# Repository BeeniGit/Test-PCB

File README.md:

# Test-PCB

```wave
<WaveDormHeader>
  {signal: [
    {name: 'clk', wave: 'p.....|...'},
    {name: 'dat', wave: 'x.345x|=.x', data: ['head', 'body', 'tail', 'data']},
    {name: 'req', wave: '0.1..0|1.0'},
    {},
    {name: 'ack', wave: '1.....|01.'}
  ]}
</WaveDormHeader>
```

```mermaid
graph LR
  A --> B;
  B --> A;
```

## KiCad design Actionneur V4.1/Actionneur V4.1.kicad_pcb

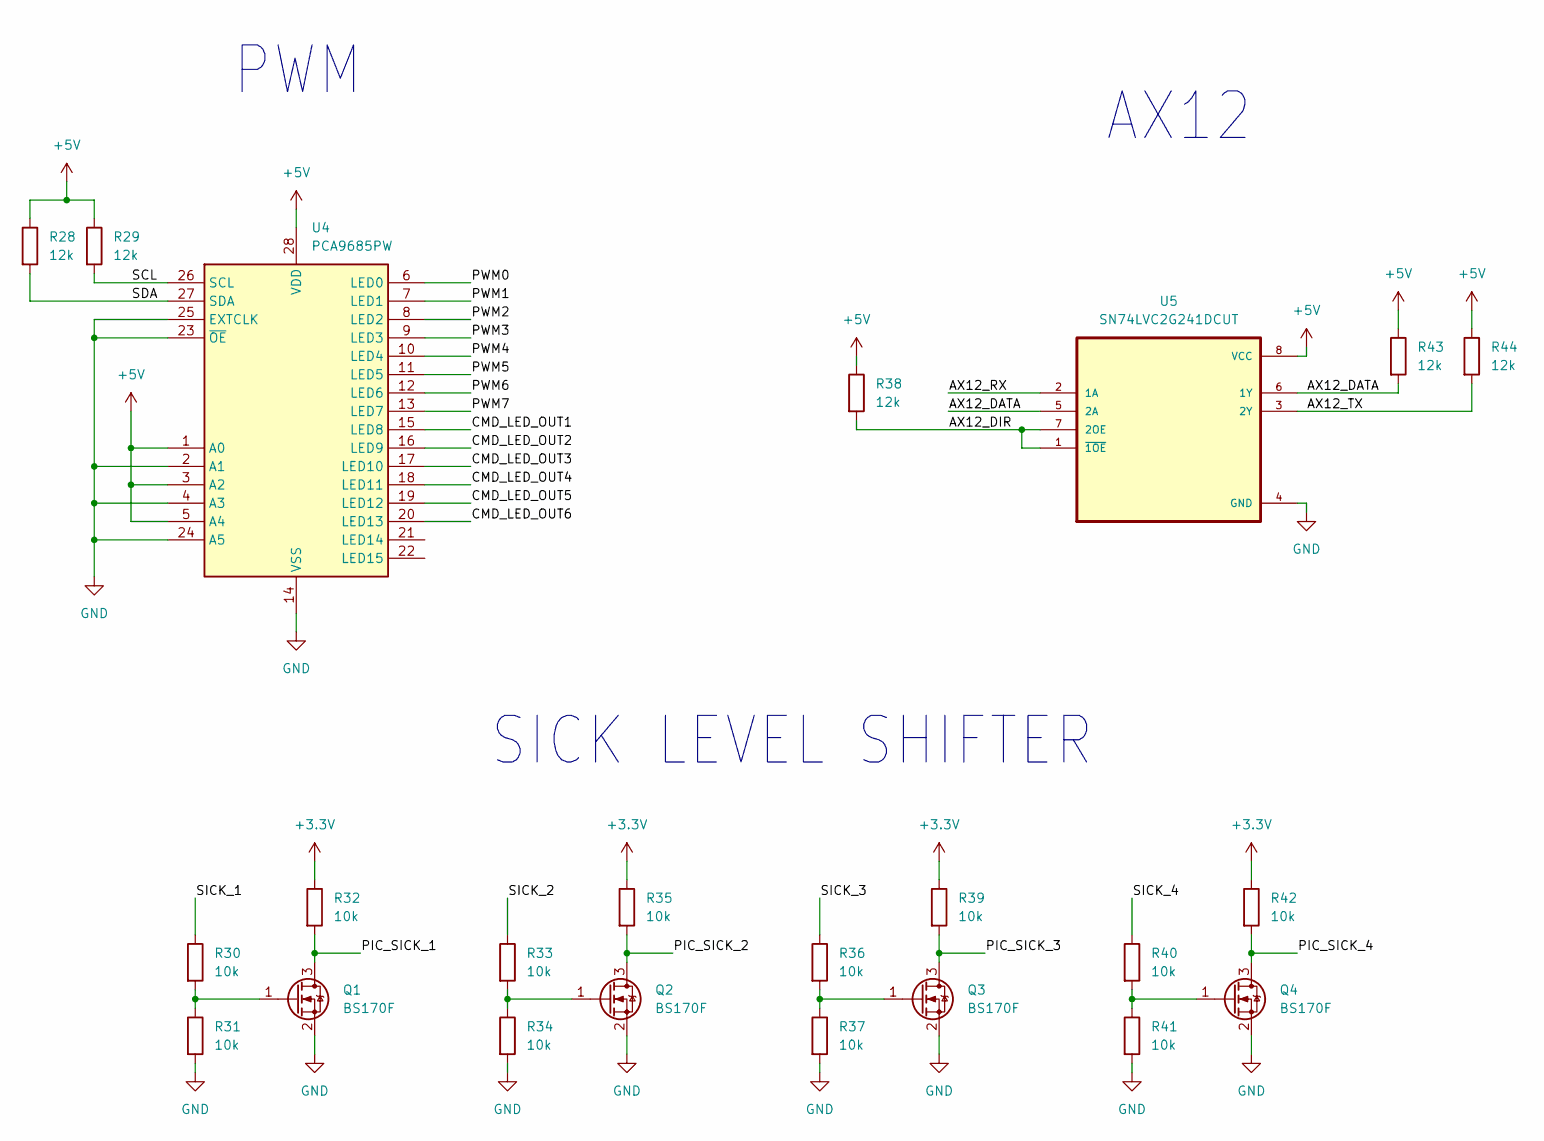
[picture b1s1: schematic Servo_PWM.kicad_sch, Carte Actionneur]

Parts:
Q1, Q2, Q3, Q4: BS170F; SOT-23
R28, R29, R38, R43, R44: 12k; R_0805_2012Metric
R30, R31, R32, R33, R34, R35, R36, R37, R39, R40, R41, R42: 10k; R_0805_2012Metric
U4: PCA9685PW; TSSOP-28_4.4x9.7mm_P0.65mm
U5: SN74LVC2G241DCUT; SOP50P310X90-8N

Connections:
+5V: R28.1, R29.1, R38.1, R43.1, R44.1, U4.1 (A0), U4.3 (A2), U4.5 (A4), U4.28 (VDD), U5.8 (VCC); also elsewhere on the board
/Servo_PWM/AX12_DATA: R43.2, U5.5 (2A), U5.6 (1Y)
/Servo_PWM/AX12_DIR: R38.2, U5.1 (~1OE), U5.7 (2OE)
/Servo_PWM/AX12_RX: U5.2 (1A)
/Servo_PWM/AX12_TX: R44.2, U5.3 (2Y)
/Servo_PWM/CMD_LED_OUT1: U4.15 (LED8)
/Servo_PWM/CMD_LED_OUT2: U4.16 (LED9)
/Servo_PWM/CMD_LED_OUT3: U4.17 (LED10)
/Servo_PWM/CMD_LED_OUT4: U4.18 (LED11)
/Servo_PWM/CMD_LED_OUT5: U4.19 (LED12)
/Servo_PWM/CMD_LED_OUT6: U4.20 (LED13)
/Servo_PWM/PIC_SICK_1: Q1.3 (D), R32.2
/Servo_PWM/PIC_SICK_2: Q2.3 (D), R35.2
/Servo_PWM/PIC_SICK_3: Q3.3 (D), R39.2
/Servo_PWM/PIC_SICK_4: Q4.3 (D), R42.2
/Servo_PWM/PWM0: U4.6 (LED0)
/Servo_PWM/PWM1: U4.7 (LED1)
/Servo_PWM/PWM2: U4.8 (LED2)
/Servo_PWM/PWM3: U4.9 (LED3)
/Servo_PWM/PWM4: U4.10 (LED4)
/Servo_PWM/PWM5: U4.11 (LED5)
/Servo_PWM/PWM6: U4.12 (LED6)
/Servo_PWM/PWM7: U4.13 (LED7)
/Servo_PWM/SCL: R29.2, U4.26 (SCL)
/Servo_PWM/SDA: R28.2, U4.27 (SDA)
/Servo_PWM/SICK_1: R30.1
/Servo_PWM/SICK_2: R33.1
/Servo_PWM/SICK_3: R36.1
/Servo_PWM/SICK_4: R40.1
GND: Q1.2 (S), Q2.2 (S), Q3.2 (S), Q4.2 (S), R31.2, R34.2, R37.2, R41.2, U4.2 (A1), U4.4 (A3), U4.14 (VSS), U4.23 (~OE), U4.24 (A5), U4.25 (EXTCLK), U5.4 (GND); also elsewhere on the board
unnamed: Q1.1 (G), R30.2, R31.1
unnamed: Q2.1 (G), R33.2, R34.1
unnamed: Q3.1 (G), R36.2, R37.1
unnamed: Q4.1 (G), R40.2, R41.1

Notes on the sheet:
AX12
SICK LEVEL SHIFTER
PWM

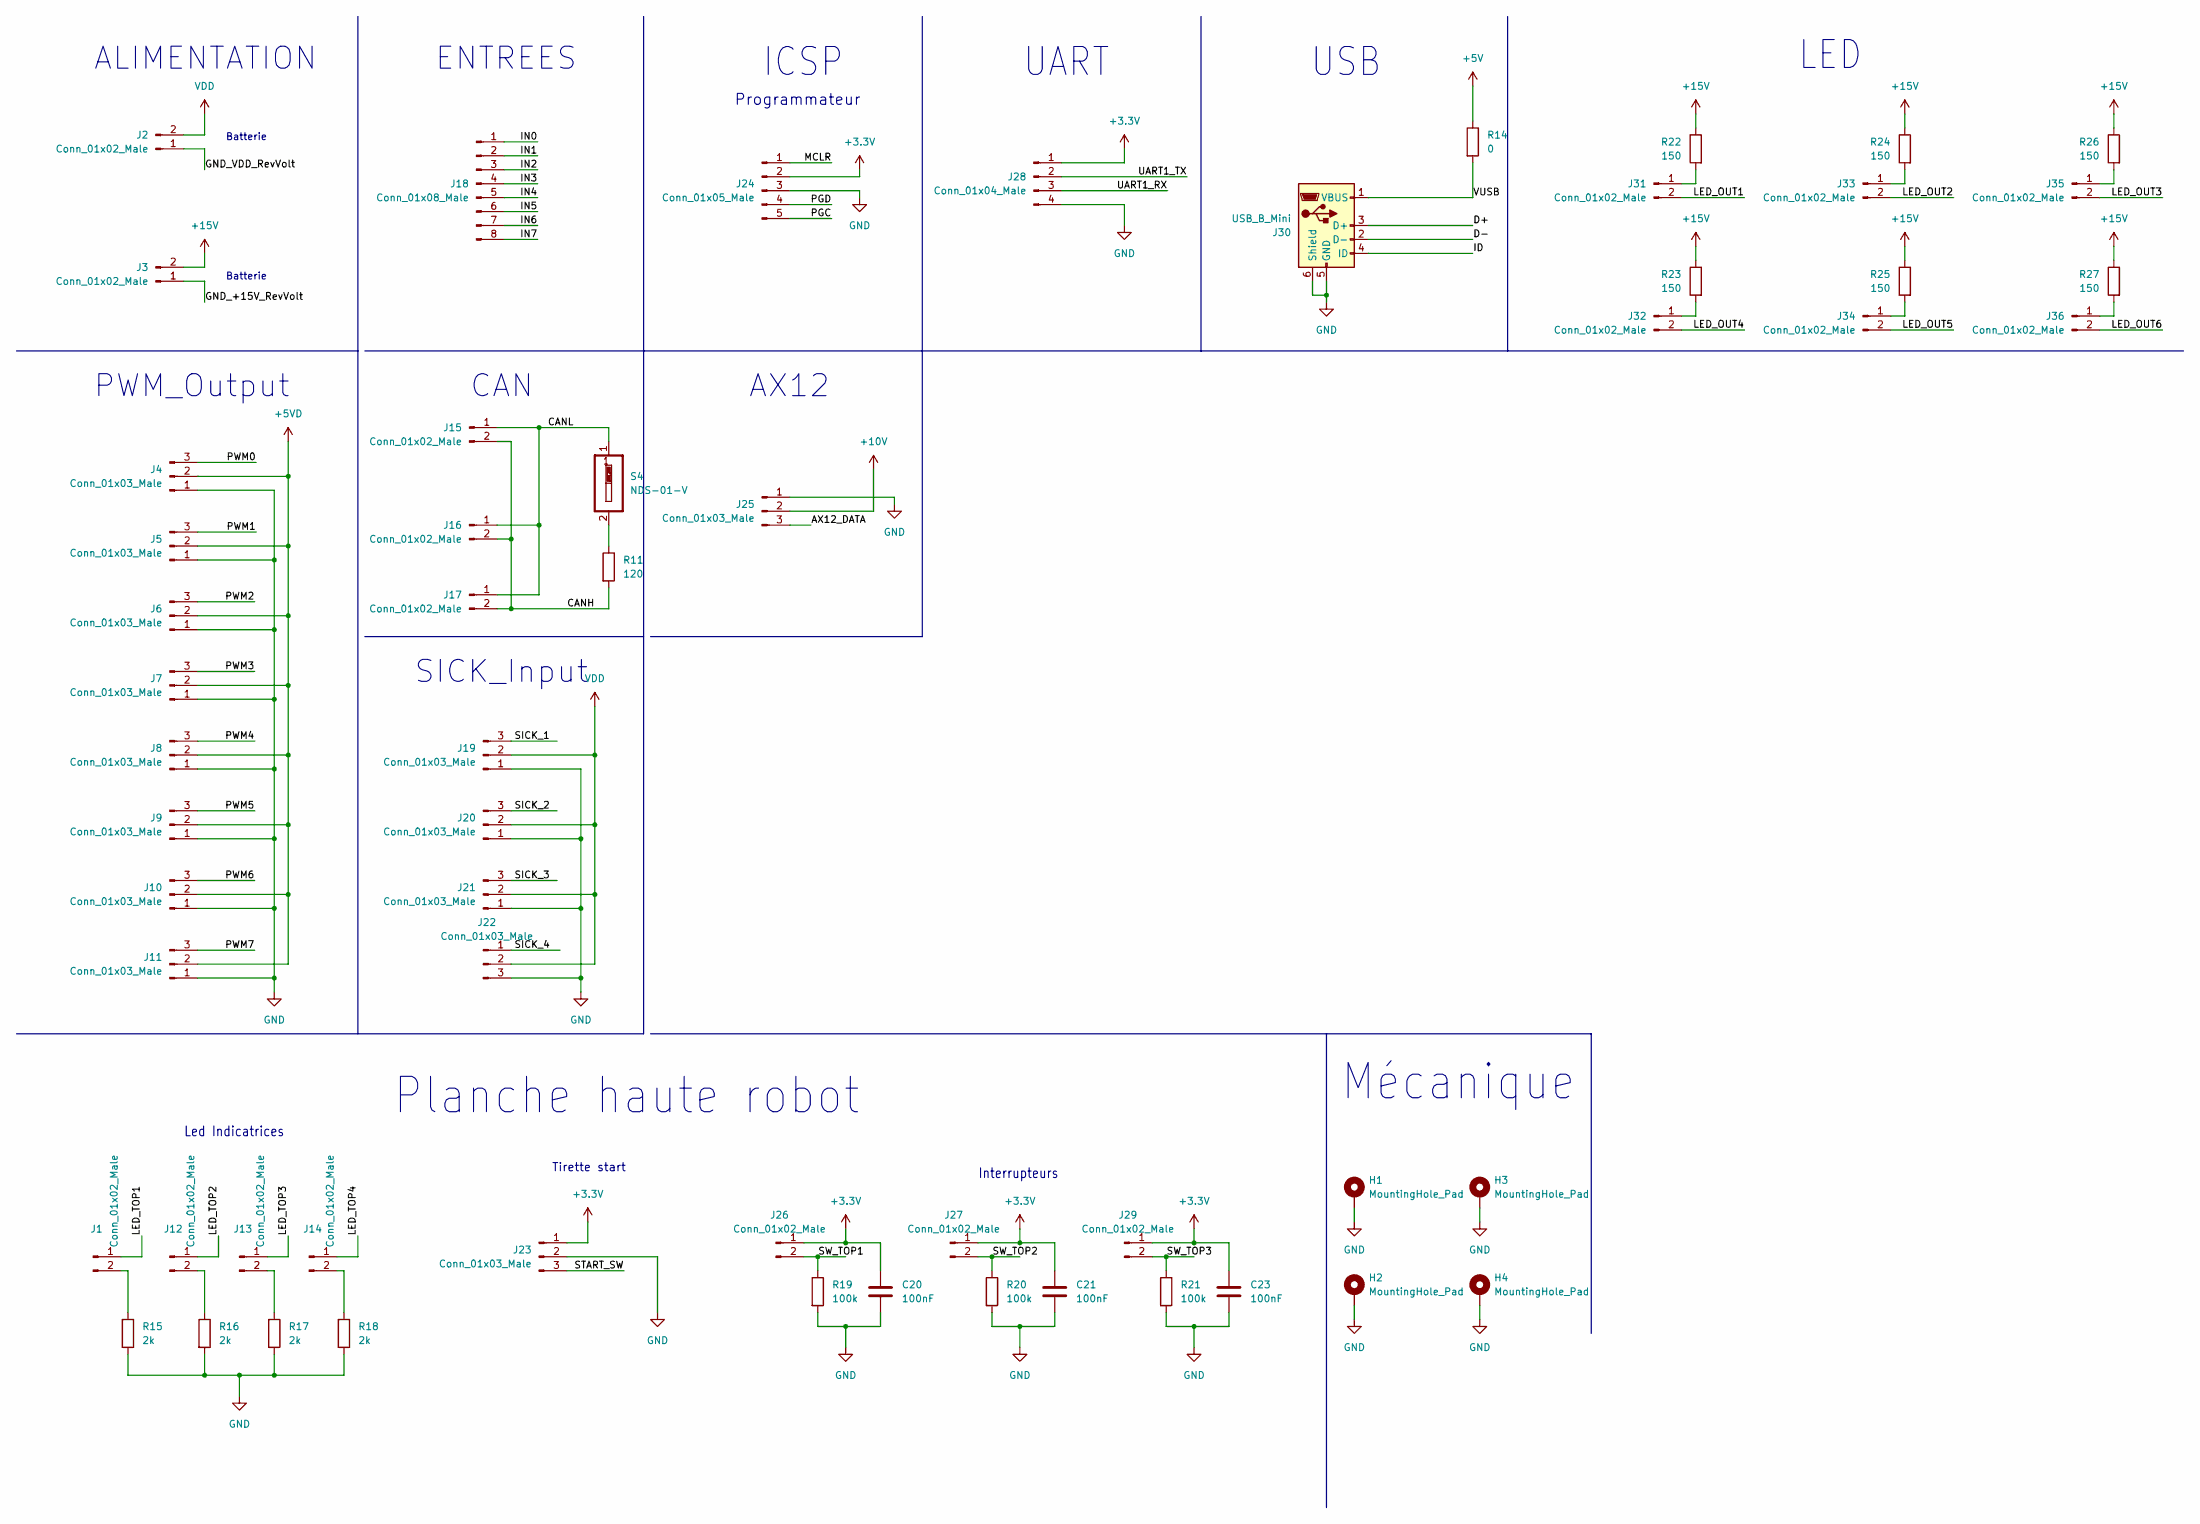
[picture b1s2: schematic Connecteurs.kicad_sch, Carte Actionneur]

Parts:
C20, C21, C23: 100nF; C_0805_2012Metric
H1, H2, H3, H4: MountingHole_Pad; MountingHole_2.2mm_M2_ISO14580_Pad
J1, J12, J13, J14, J15, J16, J17, J26, J27, J29, J31, J32, J33, J34, J35, J36: Conn_01x02_Male; FanPinHeader_1x02_P2.54mm_Vertical
J2, J3: Conn_01x02_Male; PhoenixContact_MSTBA_2,5_2-G_1x02_P5.00mm_Horizontal
J4, J5, J6, J7, J8, J9, J10, J11, J19, J20, J21, J22, J23, J25: Conn_01x03_Male; FanPinHeader_1x03_P2.54mm_Vertical
J18: Conn_01x08_Male; PinHeader_1x08_P2.54mm_Vertical
J24: Conn_01x05_Male; PinSocket_1x05_P2.54mm_Vertical
J28: Conn_01x04_Male; PinHeader_1x04_P2.54mm_Vertical
J30: USB_B_Mini; USB_Mini-B_Wuerth_65100516121_Horizontal
R11: 120; R_0805_2012Metric
R14: 0; R_0805_2012Metric
R15, R16, R17, R18: 2k; R_0805_2012Metric
R19, R20, R21: 100k; R_0805_2012Metric
R22, R23, R24, R25, R26, R27: 150; R_0805_2012Metric
S4: NDS-01-V; DIP762W60P254L390H705Q2N; Manufacturer_Part_Number NDS-01-V

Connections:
+5V: R14.1; also elsewhere on the board
+5VD: J4.2, J5.2, J6.2, J7.2, J8.2, J9.2, J10.2, J11.2; also elsewhere on the board
+10V: J25.2; also elsewhere on the board
+15V: J3.2, R22.1, R23.1, R24.1, R25.1, R26.1, R27.1; also elsewhere on the board
/Connecteurs/AX12_DATA: J25.3
/Connecteurs/CANH: J15.2, J16.2, J17.2, R11.2
/Connecteurs/CANL: J15.1, J16.1, J17.1, S4.1
/Connecteurs/D+: J30.3 (D+)
/Connecteurs/D-: J30.2 (D-)
/Connecteurs/GND_+15V_RevVolt: J3.1
/Connecteurs/GND_VDD_RevVolt: J2.1
/Connecteurs/ID: J30.4 (ID)
/Connecteurs/IN0: J18.1
/Connecteurs/IN1: J18.2
/Connecteurs/IN2: J18.3
/Connecteurs/IN3: J18.4
/Connecteurs/IN4: J18.5
/Connecteurs/IN5: J18.6
/Connecteurs/IN6: J18.7
/Connecteurs/IN7: J18.8
/Connecteurs/LED_OUT1: J31.2
/Connecteurs/LED_OUT2: J33.2
/Connecteurs/LED_OUT3: J35.2
/Connecteurs/LED_OUT4: J32.2
/Connecteurs/LED_OUT5: J34.2
/Connecteurs/LED_OUT6: J36.2
/Connecteurs/LED_TOP1: J1.1
/Connecteurs/LED_TOP2: J12.1
/Connecteurs/LED_TOP3: J13.1
/Connecteurs/LED_TOP4: J14.1
/Connecteurs/MCLR: J24.1
/Connecteurs/PGC: J24.5
/Connecteurs/PGD: J24.4
/Connecteurs/PWM0: J4.3
/Connecteurs/PWM1: J5.3
/Connecteurs/PWM2: J6.3
/Connecteurs/PWM3: J7.3
/Connecteurs/PWM4: J8.3
/Connecteurs/PWM5: J9.3
/Connecteurs/PWM6: J10.3
/Connecteurs/PWM7: J11.3
/Connecteurs/SICK_1: J19.3
/Connecteurs/SICK_2: J20.3
/Connecteurs/SICK_3: J21.3
/Connecteurs/SICK_4: J22.1
/Connecteurs/START_SW: J23.3
/Connecteurs/SW_TOP1: J26.2, R19.1
/Connecteurs/SW_TOP2: J27.2, R20.1
/Connecteurs/SW_TOP3: J29.2, R21.1
/Connecteurs/UART1_RX: J28.3
/Connecteurs/UART1_TX: J28.2
/Connecteurs/VUSB: J30.1 (VBUS), R14.2
GND: C20.2, C21.2, C23.2, H1.1, H2.1, H3.1, H4.1, J4.1, J5.1, J6.1, J7.1, J8.1, J9.1, J10.1, J11.1, J19.1, J20.1, J21.1, J22.3, J23.2, J24.3, J25.1, J28.4, J30.5 (GND), J30.6 (Shield), R15.2, R16.2, R17.2, R18.2, R19.2, R20.2, R21.2; also elsewhere on the board
unnamed: J1.2, R15.1
unnamed: J12.2, R16.1
unnamed: J13.2, R17.1
unnamed: J14.2, R18.1
unnamed: J31.1, R22.2
unnamed: J32.1, R23.2
unnamed: J33.1, R24.2
unnamed: J34.1, R25.2
unnamed: J35.1, R26.2
unnamed: J36.1, R27.2
unnamed: R11.1, S4.2
VDD: J2.2, J19.2, J20.2, J21.2, J22.2; also elsewhere on the board

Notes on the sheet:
UART
ENTREES
Batterie
CAN
ICSP
SICK_Input
PWM_Output
Led Indicatrices
LED
Interrupteurs
Batterie
Planche haute robot
Mécanique
USB
AX12
ALIMENTATION
Programmateur
Tirette start

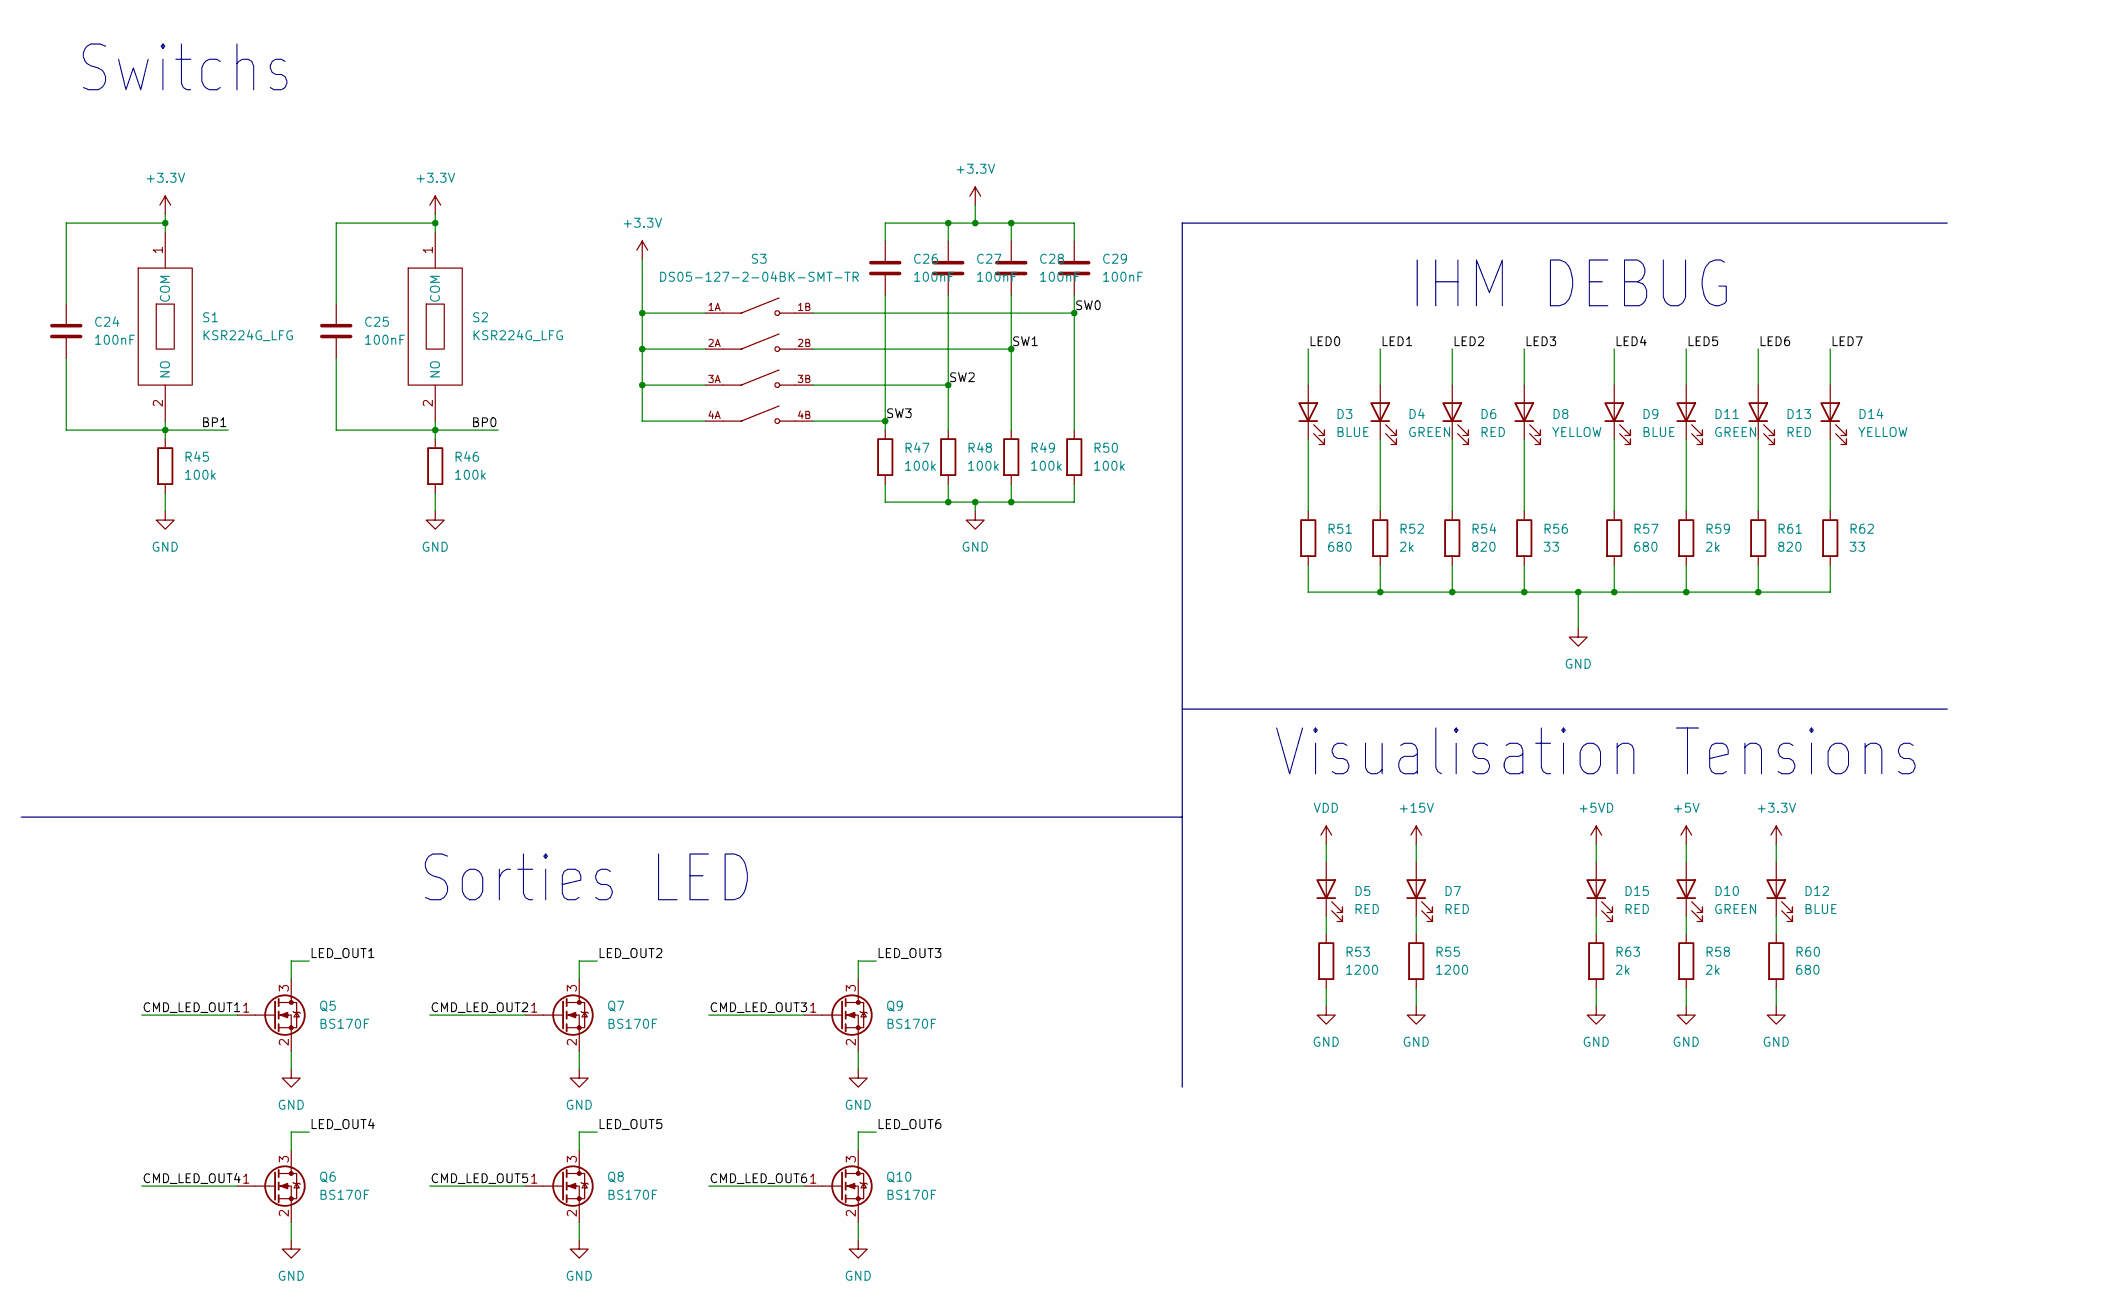
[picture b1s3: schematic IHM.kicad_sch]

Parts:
C24, C25, C26, C27, C28, C29: 100nF; C_0805_2012Metric
D3, D9, D12: BLUE; LED_0805_2012Metric
D4, D10, D11: GREEN; LED_0805_2012Metric
D5, D6, D7, D13, D15: RED; LED_0805_2012Metric
D8, D14: YELLOW; LED_0805_2012Metric
Q5, Q6, Q7, Q8, Q9, Q10: BS170F; SOT-23
R45, R46, R47, R48, R49, R50: 100k; R_0805_2012Metric
R51, R57, R60: 680; R_0805_2012Metric
R52, R58, R59, R63: 2k; R_0805_2012Metric
R53, R55: 1200; R_0805_2012Metric
R54, R61: 820; R_0805_2012Metric
R56, R62: 33; R_0805_2012Metric
S1, S2: KSR224G_LFG; KSR224GLFG; Manufacturer_Part_Number KSR224G LFG
S3: DS05-127-2-04BK-SMT-TR; SW_DS05-127-2-04BK-SMT-TR; PARTREV V0.0

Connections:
+5V: D10.2 (A); also elsewhere on the board
+5VD: D15.2 (A); also elsewhere on the board
+15V: D7.2 (A); also elsewhere on the board
/IHM/BP0: C25.2, R46.1, S2.2 (NO)
/IHM/BP1: C24.2, R45.1, S1.2 (NO)
/IHM/CMD_LED_OUT1: Q5.1 (G)
/IHM/CMD_LED_OUT2: Q7.1 (G)
/IHM/CMD_LED_OUT3: Q9.1 (G)
/IHM/CMD_LED_OUT4: Q6.1 (G)
/IHM/CMD_LED_OUT5: Q8.1 (G)
/IHM/CMD_LED_OUT6: Q10.1 (G)
/IHM/LED0: D3.2 (A)
/IHM/LED1: D4.2 (A)
/IHM/LED2: D6.2 (A)
/IHM/LED3: D8.2 (A)
/IHM/LED4: D9.2 (A)
/IHM/LED5: D11.2 (A)
/IHM/LED6: D13.2 (A)
/IHM/LED7: D14.2 (A)
/IHM/LED_OUT1: Q5.3 (D)
/IHM/LED_OUT2: Q7.3 (D)
/IHM/LED_OUT3: Q9.3 (D)
/IHM/LED_OUT4: Q6.3 (D)
/IHM/LED_OUT5: Q8.3 (D)
/IHM/LED_OUT6: Q10.3 (D)
/IHM/SW3: C26.2, R47.1, S3.4B
GND: Q5.2 (S), Q6.2 (S), Q7.2 (S), Q8.2 (S), Q9.2 (S), Q10.2 (S), R45.2, R46.2, R47.2, R48.2, R49.2, R50.2, R51.2, R52.2, R53.2, R54.2, R55.2, R56.2, R57.2, R58.2, R59.2, R60.2, R61.2, R62.2, R63.2; also elsewhere on the board
unnamed: D3.1 (K), R51.1
unnamed: D4.1 (K), R52.1
unnamed: D5.1 (K), R53.1
unnamed: D6.1 (K), R54.1
unnamed: D7.1 (K), R55.1
unnamed: D8.1 (K), R56.1
unnamed: D9.1 (K), R57.1
unnamed: D10.1 (K), R58.1
unnamed: D11.1 (K), R59.1
unnamed: D12.1 (K), R60.1
unnamed: D13.1 (K), R61.1
unnamed: D14.1 (K), R62.1
unnamed: D15.1 (K), R63.1
VDD: D5.2 (A); also elsewhere on the board

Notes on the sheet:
Switchs
IHM DEBUG
Sorties LED
Visualisation Tensions

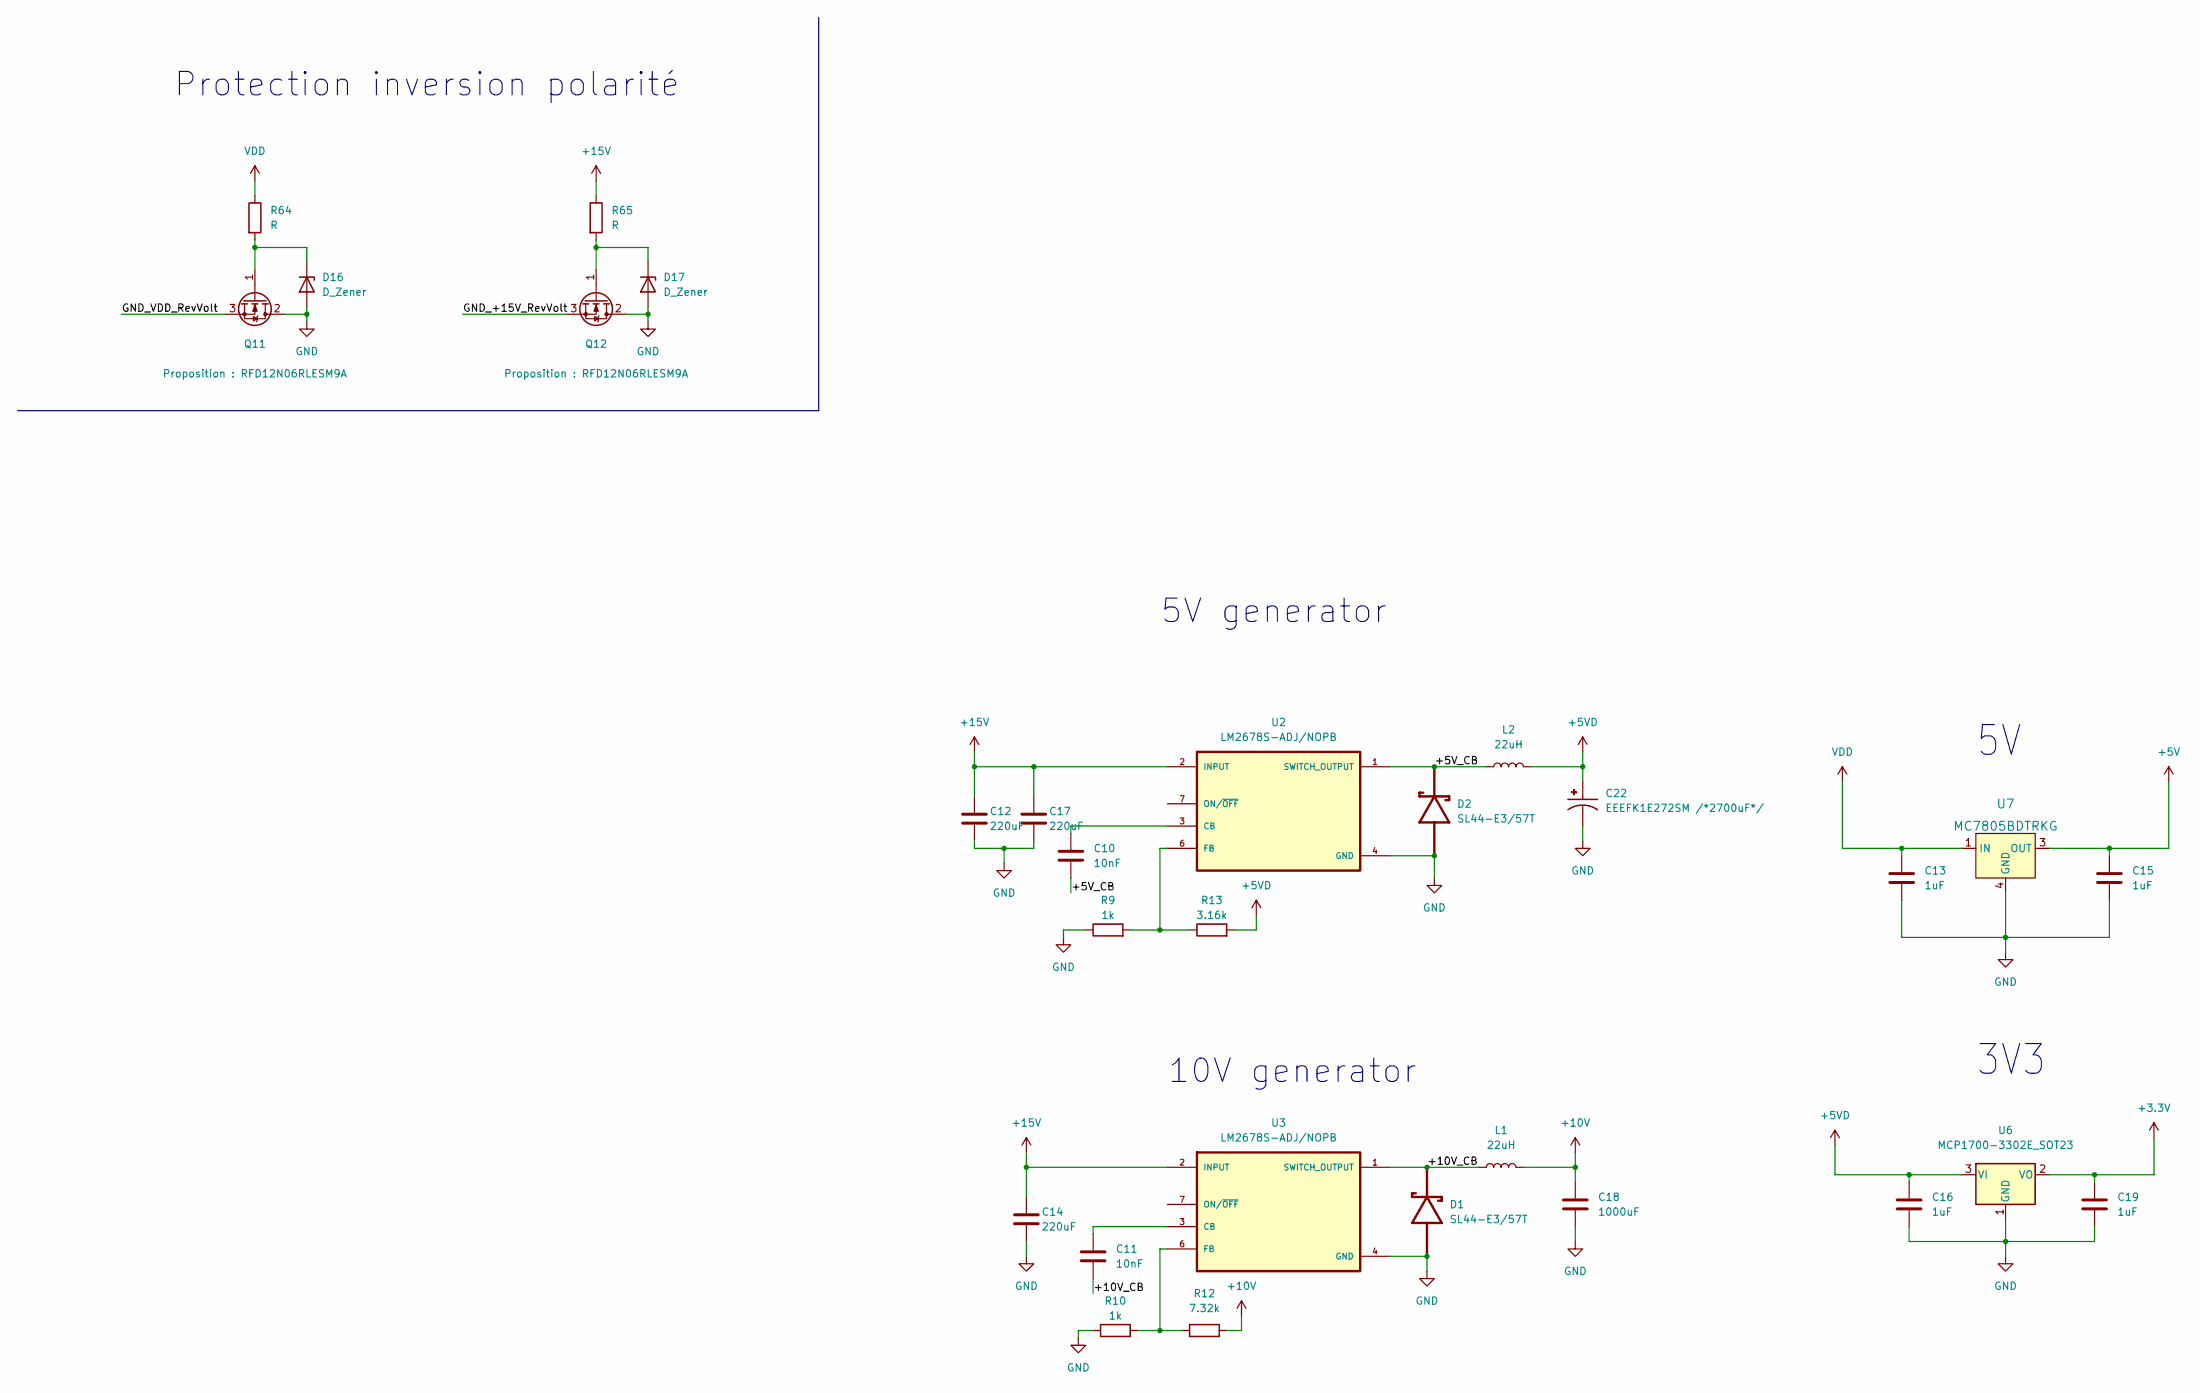
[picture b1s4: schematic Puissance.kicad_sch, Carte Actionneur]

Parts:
C10, C11: 10nF; C_0805_2012Metric
C12, C14, C17: 220uF; C_Elec_6.3x7.7
C13, C15, C16, C19: 1uF; C_0805_2012Metric
C18: 1000uF; C_Elec_8x10.2
C22: EEEFK1E272SM /*2700uF*/; CAP_EEEFK1E272SM; PARTREV 10-Oct-19
D1, D2: SL44-E3/57T; DIOM7959X262N
D16, D17: D_Zener; D_SMA
L1, L2: 22uH; L_12x12mm_H8mm
Q11, Q12: Proposition : RFD12N06RLESM9A; TO-263-2
R9, R10: 1k; R_0805_2012Metric
R12: 7.32k; R_0805_2012Metric
R13: 3.16k; R_0805_2012Metric
R64, R65: R; R_0805_2012Metric
U2, U3: LM2678S-ADJ/NOPB; TO127P1435X464-8N
U6: MCP1700-3302E_SOT23; SOT-23
U7: MC7805BDTRKG; TO-252-3; MPN MC7805BDTRKG; Digi-Key_PN MC7805BDTRKGOSCT-ND

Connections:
+5V: C15.1, U7.3 (OUT); also elsewhere on the board
+5VD: C16.1, C22.1, L2.2, R13.2, U6.3 (VI); also elsewhere on the board
+10V: C18.1, L1.2, R12.2; also elsewhere on the board
+15V: C12.1, C14.1, C17.1, R65.1, U2.2 (INPUT), U3.2 (INPUT); also elsewhere on the board
/Puissance/+5V_CB: C10.2, D2.C, L2.1, U2.1 (SWITCH_OUTPUT)
/Puissance/+10V_CB: C11.2, D1.C, L1.1, U3.1 (SWITCH_OUTPUT)
/Puissance/GND_+15V_RevVolt: Q12.3 (S)
/Puissance/GND_VDD_RevVolt: Q11.3 (S)
GND: C12.2, C13.2, C14.2, C15.2, C16.2, C17.2, C18.2, C19.2, C22.2, D1.A, D2.A, D16.2 (A), D17.2 (A), Q11.2 (D), Q12.2 (D), R9.1, R10.1, U2.4 (GND), U3.4 (GND), U6.1 (GND), U7.4 (GND); also elsewhere on the board
unnamed: C10.1, U2.3 (CB)
unnamed: C11.1, U3.3 (CB)
unnamed: D16.1 (K), Q11.1 (G), R64.2
unnamed: D17.1 (K), Q12.1 (G), R65.2
unnamed: R10.2, R12.1, U3.6 (FB)
unnamed: R9.2, R13.1, U2.6 (FB)
VDD: C13.1, R64.1, U7.1 (IN); also elsewhere on the board

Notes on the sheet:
10V generator
3V3
Protection inversion polarité
5V generator

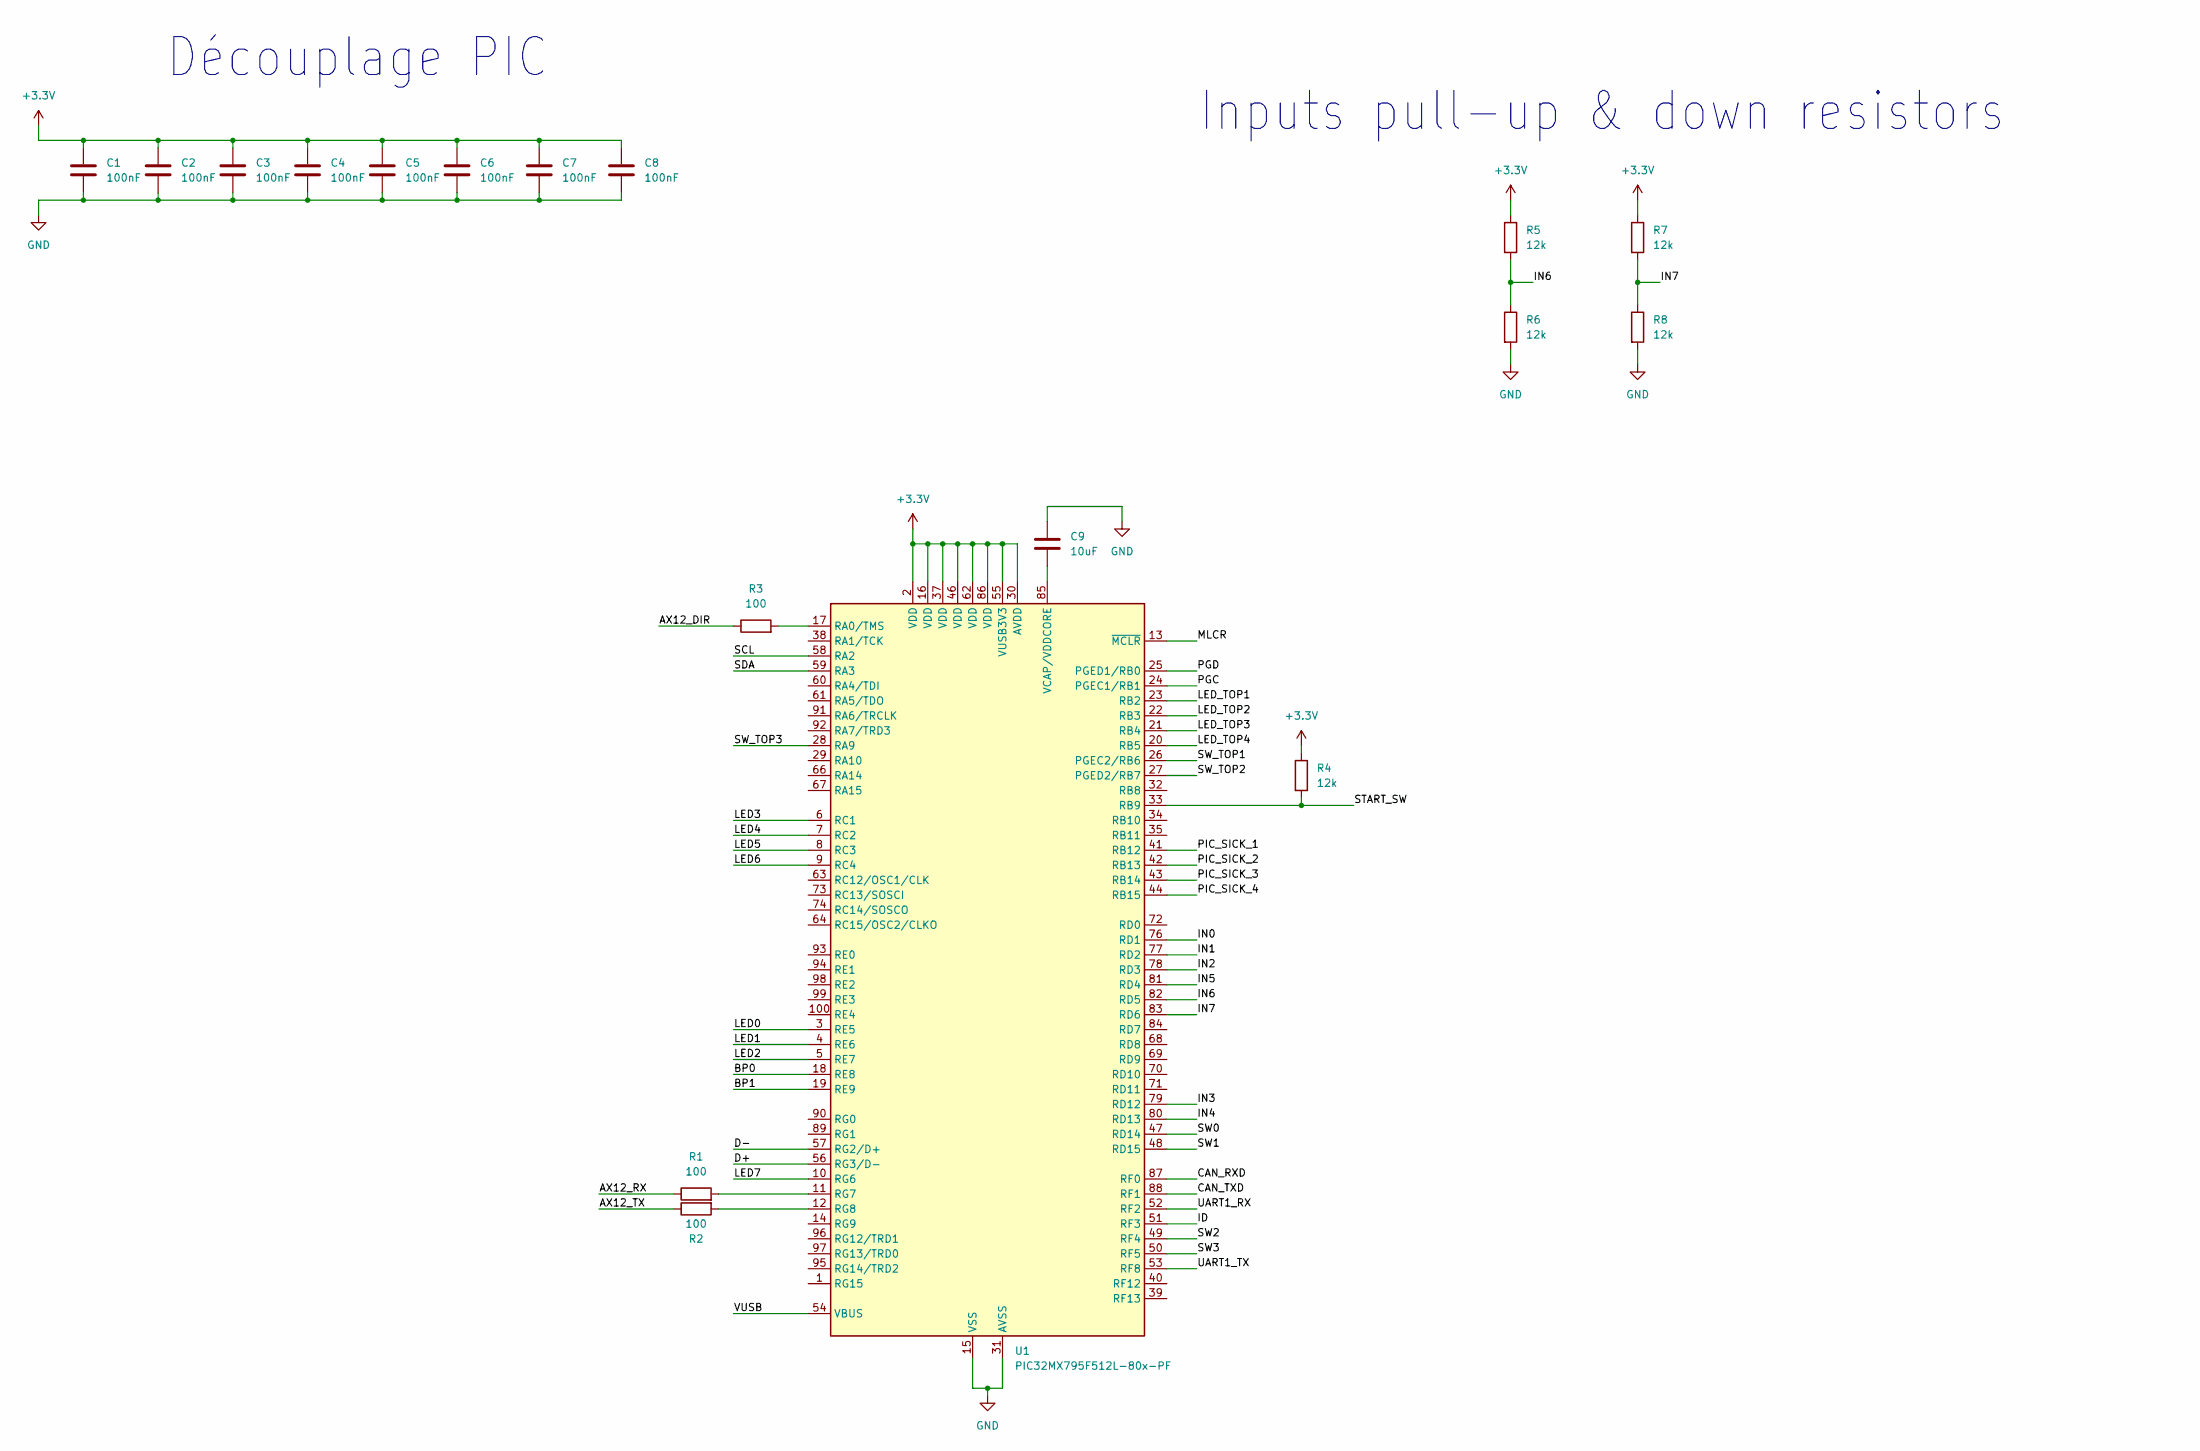
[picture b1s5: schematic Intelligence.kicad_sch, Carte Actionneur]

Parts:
C1, C2, C3, C4, C5, C6, C7, C8: 100nF; C_0805_2012Metric
C9: 10uF; C_0805_2012Metric
R1, R2, R3: 100; R_0805_2012Metric
R4, R5, R6, R7, R8: 12k; R_0805_2012Metric
U1: PIC32MX795F512L-80x-PF; TQFP-100_14x14mm_P0.5mm

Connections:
/Intelligence/AX12_DIR: R3.1
/Intelligence/AX12_RX: R1.1
/Intelligence/AX12_TX: R2.1
/Intelligence/BP0: U1.18 (RE8)
/Intelligence/BP1: U1.19 (RE9)
/Intelligence/CAN_RXD: U1.87 (RF0)
/Intelligence/CAN_TXD: U1.88 (RF1)
/Intelligence/D+: U1.56 (RG3/D-)
/Intelligence/D-: U1.57 (RG2/D+)
/Intelligence/ID: U1.51 (RF3)
/Intelligence/IN0: U1.76 (RD1)
/Intelligence/IN1: U1.77 (RD2)
/Intelligence/IN2: U1.78 (RD3)
/Intelligence/IN3: U1.79 (RD12)
/Intelligence/IN4: U1.80 (RD13)
/Intelligence/IN5: U1.81 (RD4)
/Intelligence/IN6: R5.2, R6.1, U1.82 (RD5)
/Intelligence/IN7: R7.2, R8.1, U1.83 (RD6)
/Intelligence/LED0: U1.3 (RE5)
/Intelligence/LED1: U1.4 (RE6)
/Intelligence/LED2: U1.5 (RE7)
/Intelligence/LED3: U1.6 (RC1)
/Intelligence/LED4: U1.7 (RC2)
/Intelligence/LED5: U1.8 (RC3)
/Intelligence/LED6: U1.9 (RC4)
/Intelligence/LED7: U1.10 (RG6)
/Intelligence/LED_TOP1: U1.23 (RB2)
/Intelligence/LED_TOP2: U1.22 (RB3)
/Intelligence/LED_TOP3: U1.21 (RB4)
/Intelligence/LED_TOP4: U1.20 (RB5)
/Intelligence/MLCR: U1.13 (~MCLR)
/Intelligence/PGC: U1.24 (PGEC1/RB1)
/Intelligence/PGD: U1.25 (PGED1/RB0)
/Intelligence/PIC_SICK_1: U1.41 (RB12)
/Intelligence/PIC_SICK_2: U1.42 (RB13)
/Intelligence/PIC_SICK_3: U1.43 (RB14)
/Intelligence/PIC_SICK_4: U1.44 (RB15)
/Intelligence/SCL: U1.58 (RA2)
/Intelligence/SDA: U1.59 (RA3)
/Intelligence/START_SW: R4.2, U1.33 (RB9)
/Intelligence/SW0: U1.47 (RD14)
/Intelligence/SW1: U1.48 (RD15)
/Intelligence/SW2: U1.49 (RF4)
/Intelligence/SW3: U1.50 (RF5)
/Intelligence/SW_TOP1: U1.26 (PGEC2/RB6)
/Intelligence/SW_TOP2: U1.27 (PGED2/RB7)
/Intelligence/SW_TOP3: U1.28 (RA9)
/Intelligence/UART1_RX: U1.52 (RF2)
/Intelligence/UART1_TX: U1.53 (RF8)
/Intelligence/VUSB: U1.54 (VBUS)
GND: C1.2, C2.2, C3.2, C4.2, C5.2, C6.2, C7.2, C8.2, C9.1, R6.2, R8.2, U1.15 (VSS), U1.31 (AVSS), U1.36 (VSS), U1.45 (VSS), U1.65 (VSS), U1.75 (VSS); also elsewhere on the board
unnamed: C9.2, U1.85 (VCAP/VDDCORE)
unnamed: R1.2, U1.11 (RG7)
unnamed: R2.2, U1.12 (RG8)
unnamed: R3.2, U1.17 (RA0/TMS)

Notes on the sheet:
Découplage PIC
Inputs pull-up & down resistors

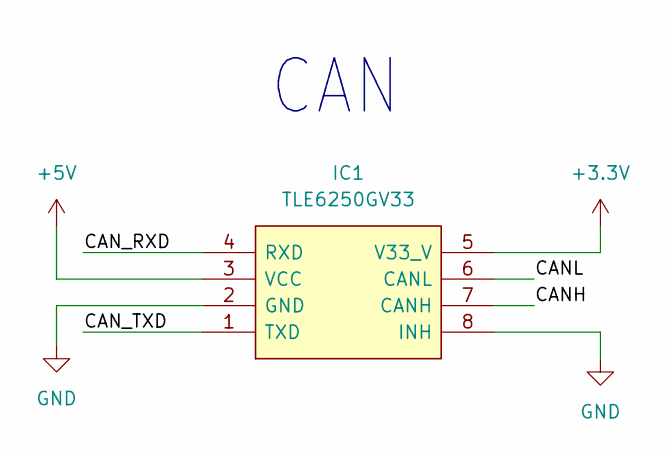
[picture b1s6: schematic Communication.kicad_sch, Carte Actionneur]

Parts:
IC1: TLE6250GV33; SOIC127P600X175-8N; Manufacturer_Part_Number TLE6250GV33

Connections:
+5V: IC1.3 (VCC); also elsewhere on the board
/Communication/CANH: IC1.7 (CANH)
/Communication/CANL: IC1.6 (CANL)
/Communication/CAN_RXD: IC1.4 (RXD)
/Communication/CAN_TXD: IC1.1 (TXD)
GND: IC1.2 (GND), IC1.8 (INH); also elsewhere on the board

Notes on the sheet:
CAN

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
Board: 2 copper layers, 189 parts (0 on the bottom side), 73 nets, no tracks yet.

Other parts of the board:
C26#2, C27#2, C28#2, C29#2: 100nF; C_0805_2012Metric
R47#2, R48#2, R49#2, R50#2: 100k; R_0805_2012Metric
S3#2, S4#2, S5, S6: NDS-01-V; DIP762W60P254L390H705Q2N

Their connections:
GND: R47#2.2, R48#2.2, R49#2.2, R50#2.2; also elsewhere on the board

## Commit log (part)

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2022-11-05 First
